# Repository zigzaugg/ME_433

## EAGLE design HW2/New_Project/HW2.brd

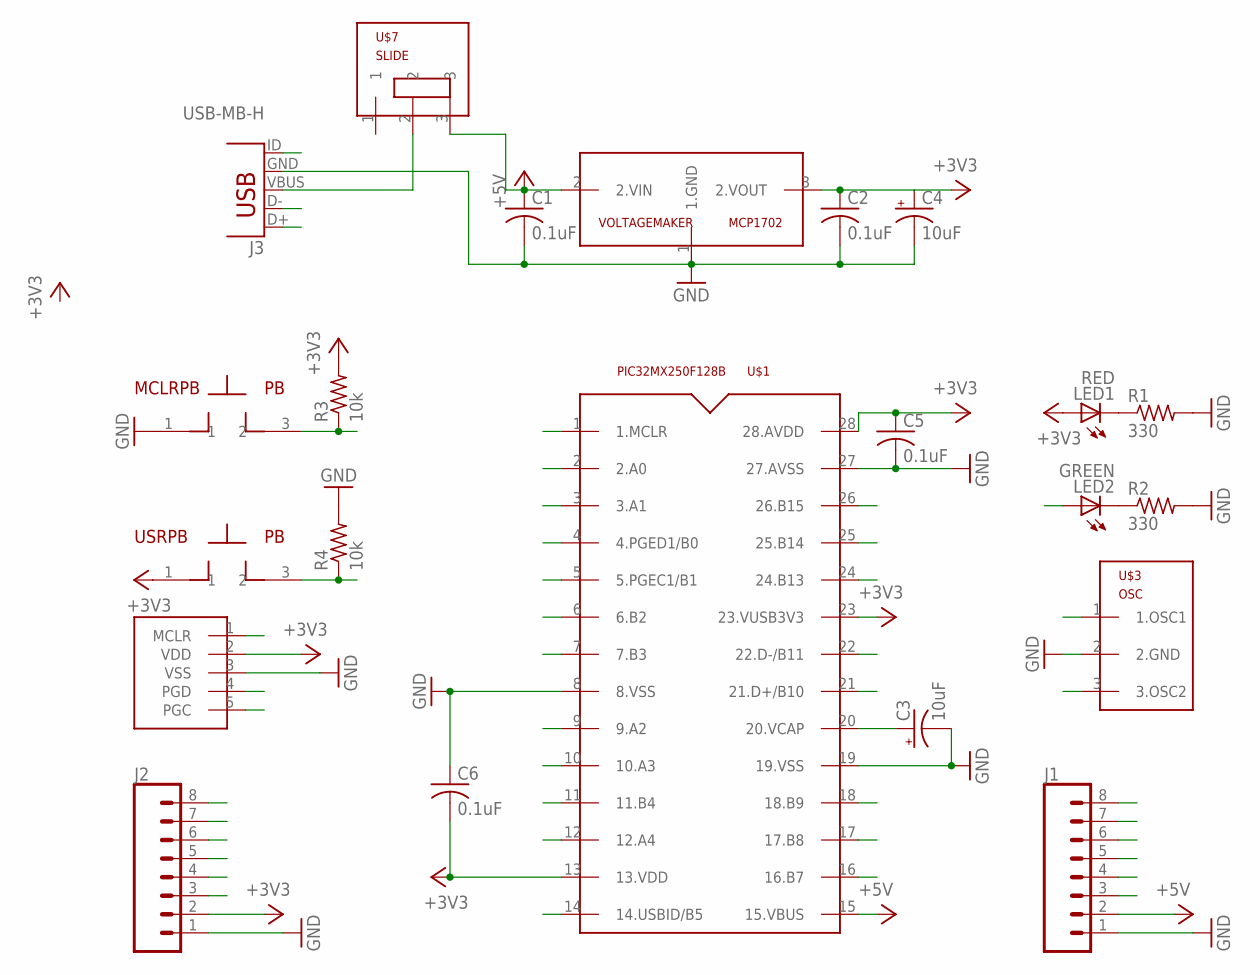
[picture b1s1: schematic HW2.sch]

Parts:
C1, C2, C5, C6: 0.1uF; C025-025X050
C3, C4: 10uF; B45181B
J1, J2: CONN_08"; 1X08
J3: USB-MB-H
LED1: RED; LED3MM
LED2: GREEN; LED3MM
MCLRPB: PB
R1, R2: 330; 0204/7
R3, R4: 10k; 0204/7
U$1: PIC32MX250F128B; DIL28-3
U$3: OSC
U$6: PICKIT
U$7: SLIDE
USRPB: PB
VOLTAGEMAKER: MCP1702; TO92

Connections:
+3V3: C2.1, C4.+, C5.1, C6.2, J2.2, LED1.A, R3.2, U$1.13 (13.VDD), U$1.23 (23.VUSB3V3), U$1.28 (28.AVDD), U$6.2 (VDD), USRPB.1, VOLTAGEMAKER.3 (2.VOUT)
+5V: C1.1, J1.2, U$1.15 (15.VBUS), U$7.3, VOLTAGEMAKER.2 (2.VIN)
A0: J2.8, U$1.2 (2.A0)
A1: J2.7, U$1.3 (3.A1)
A2: U$1.9 (9.A2), U$3.1 (1.OSC1)
A3: U$1.10 (10.A3), U$3.3 (3.OSC2)
A4: J2.3, LED2.A, U$1.12 (12.A4)
B2: J2.6, U$1.6 (6.B2)
B3: J2.5, U$1.7 (7.B3)
B4: J2.4, R4.1, U$1.11 (11.B4), USRPB.3 (2)
B7: J1.3, U$1.16 (16.B7)
B8: J1.4, U$1.17 (17.B8)
B9: J1.5, U$1.18 (18.B9)
B13: J1.6, U$1.24 (24.B13)
B14: J1.7, U$1.25 (25.B14)
B15: J1.8, U$1.26 (26.B15)
D+: J3.D+, U$1.21 (21.D+/B10)
D-: J3.D-, U$1.22 (22.D-/B11)
GND: C1.2, C2.2, C3.-, C4.-, C5.2, C6.1, J1.1, J2.1, J3.GND, MCLRPB.1, R1.2, R2.2, R4.2, U$1.8 (8.VSS), U$1.19 (19.VSS), U$1.27 (27.AVSS), U$3.2 (2.GND), U$6.3 (VSS), VOLTAGEMAKER.1 (1.GND)
ID: J3.ID, U$1.14 (14.USBID/B5)
MCLR: MCLRPB.3 (2), R3.1, U$1.1 (1.MCLR), U$6.1 (MCLR)
unnamed: J3.VBUS, U$7.2
unnamed: LED1.K (C), R1.1
unnamed: C3.+, U$1.20 (20.VCAP)
unnamed: LED2.K (C), R2.1
PGC: U$1.5 (5.PGEC1/B1), U$6.5 (PGC)
PGD: U$1.4 (4.PGED1/B0), U$6.4 (PGD)

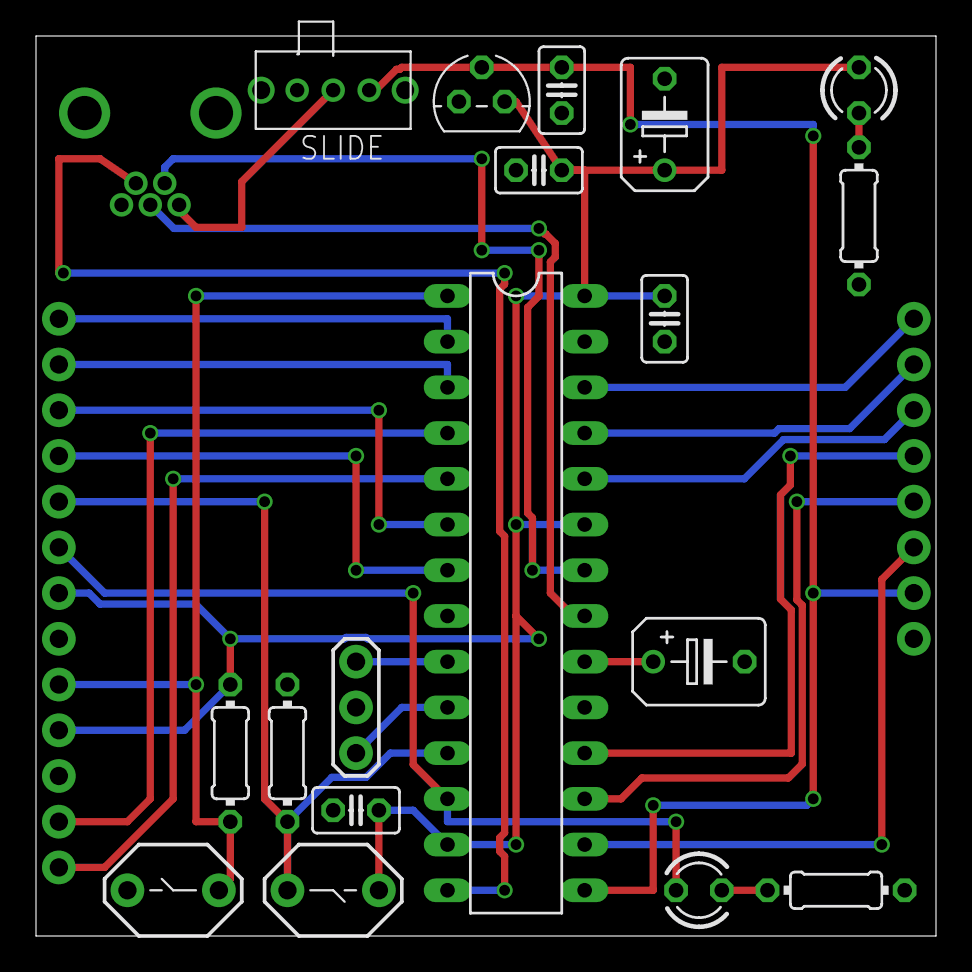
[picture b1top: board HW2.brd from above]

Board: 2 copper layers, 50.0 x 50.0 mm, 22 parts (0 on the bottom side), 27 nets.

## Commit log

2017-03-28 pics and project start
2017-03-28 Full template
2017-03-30 added new pics
2017-04-02 new pics, fixed code
2017-04-04 added eagle library
2017-04-04 lib final
2017-04-04 full sch
2017-04-06 added board
2017-04-06 gerber files
2017-04-11 added hw4
2017-04-18 added hw6 and dac working
2017-04-25 SOMEHOW IT WORKS I CHANGED NOTHING
2017-04-29 added hw6
2017-05-01 making changes
2017-05-07 hw7 had a loose resistor but now it works wow.....' :
2017-05-09 hw7 works now... unsigned issue
2017-05-09 redid hw8 and completed it
2017-05-11 added 2 android projets
2017-05-19 my computer may be broken
2017-05-30 homework 10 submit
2017-05-30 homework 16 pics
2017-05-30 fixed hw14
2017-06-06 added 15-17
2017-06-06 did 18
2017-06-06 finished 19
2017-06-08 all done! 3rd/40
